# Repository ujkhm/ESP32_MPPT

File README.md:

# 微型發電機測試機 / Micro Generator Test Machine

以 **ESP32** 為核心的小型有刷直流發電機**特性量測機台**，不是 MPPT 控制器。

主動力 775 馬達把待測發電機帶到指定轉速後，依序量測連續安全電流、內阻與開路常數，再算出固定測試電阻上的功率曲線與可用轉速上限，上位機可存成 PDF 報表。

## 倉庫結構

```
micro-generator-test-machine
├── 3D_print_Component/   變速箱與機構 3D 模型（外殼 STL 另補）
├── BOM/                  元件清單與互動式 BOM
├── KiCad/                原理圖、PCB、Gerber
├── VSCode/esp32_code/    ESP32 韌體（PlatformIO）
└── Host computer/        免安裝上位機執行檔與說明
```

各資料夾內另有說明。

## 上位機

`Host computer/MicroGeneratorHost.exe` 免安裝。複製該資料夾到 Windows 電腦，雙擊執行，依畫面以藍牙連接下位機即可測試。詳見 [Host computer/README.md](./Host%20computer/README.md)。

## 目前狀態

- 電路與 PCB：完成（見 `KiCad/`、`BOM/`）
- 韌體量測流程：完成（安全電流、內阻、曲線）
- 上位機：完成（藍牙監控與 PDF 報表）
- 外殼：待補 STL

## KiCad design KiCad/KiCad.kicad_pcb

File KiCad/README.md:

## KiCad

本專案電路使用KiCad 9做開發，無修改原理圖/PCB需求的可以直接使用資料夾內的Gerber.zip檔直接提交給板廠製板<br><br>
附上原理突及PCB快照<br>
[原理圖](images/KiCad.pdf)<br>
[PCB](images/KiCad_PCB.pdf)<br>
建議下載後用 PDF 檢視工具開啟。快照位於 `KiCad/images/`。
另有BOM表單位於BOM資料夾下[點我前往](../BOM/README.md)<br>
[回到主頁](../README.md)

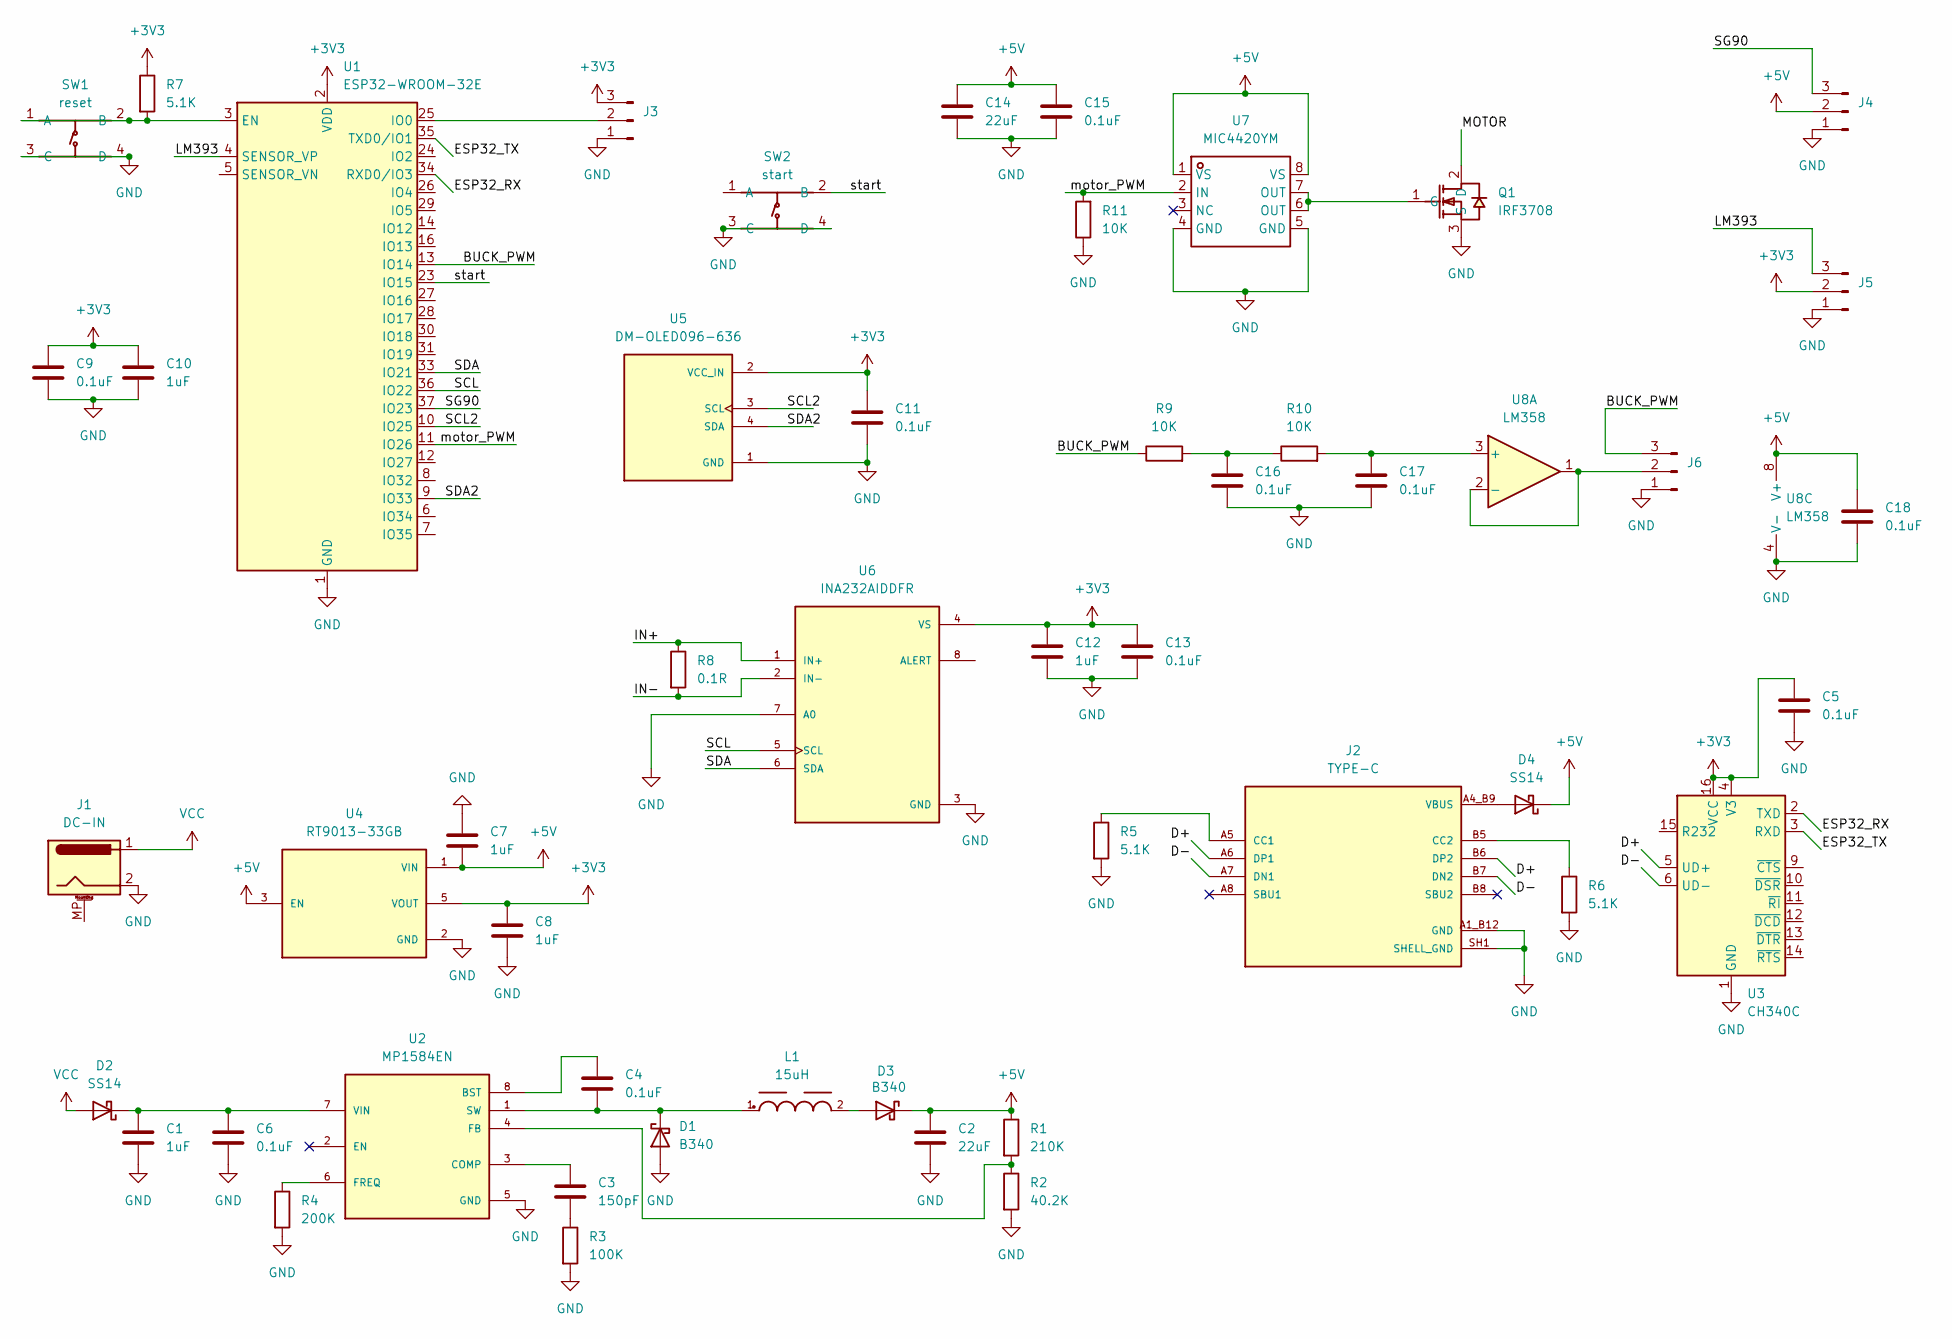
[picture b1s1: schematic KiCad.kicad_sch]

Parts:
C1, C7, C8, C10, C12: 1uF; C_0603_1608Metric
C2, C14: 22uF; C_0805_2012Metric
C3: 150pF; C_0603_1608Metric
C4, C5, C6, C9, C11, C13, C15, C16, C17, C18: 0.1uF; C_0603_1608Metric
D1, D3: B340; D_SMC
D2, D4: SS14; D_SMA
J1: DC-IN; BarrelJack_Kycon_KLDX-0202-xC_Horizontal
J2: TYPE-C; GCT_USB4105-GF-A; PARTREV B4
J3, J4, J5, J6: Conn_01x03_Pin; PinHeader_1x03_P2.54mm_Vertical
L1: 15uH; WE-PD_1260
Q1: IRF3708; TO-220-3_L10.0-W4.6-P2.54-L; LCSC Part C18212457
R1: 210K; R_0603_1608Metric
R2: 40.2K; R_0603_1608Metric
R3: 100K; R_0603_1608Metric
R4: 200K; R_0603_1608Metric
R5, R6, R7: 5.1K; R_0603_1608Metric
R8: 0.1R; R_2512_6332Metric
R9, R10, R11: 10K; R_0603_1608Metric
SW1: reset; SW-TH_4P-L6.0-W6.0-P4.50-LS6.5; LCSC Part C393938
SW2: start; SW-TH_4P-L6.0-W6.0-P4.50-LS6.5; LCSC Part C393938
U1: ESP32-WROOM-32E; ESP32-WROOM-32D
U2: MP1584EN; SOIC127P600X170-9N
U3: CH340C; SOIC-16_3.9x9.9mm_P1.27mm
U4: RT9013-33GB; SOT94P279X129-5N; PARTREV Aprill 2011
U5: DM-OLED096-636; MODULE_DM-OLED096-636; PARTREV 2018-09-10
U6: INA232AIDDFR; SOT65P280X110-8N; PARTREV December 2022
U7: MIC4420YM; SOIC-8_L4.9-W3.9-P1.27-LS6.0-BL; LCSC Part C637530
U8: LM358; SOIC-8_5.3x6.2mm_P1.27mm

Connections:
+3V3: C5.1, C8.1, C9.1, C10.1, C11.1, C12.1, C13.1, J3.3, J5.2, R7.1, U1.2 (VDD), U3.4 (V3), U3.16 (VCC), U4.5 (VOUT), U5.2 (VCC_IN), U6.4 (VS)
+5V: C2.1, C7.2, C14.1, C15.1, C18.1, D3.1 (K), D4.1 (K), J4.2, R1.1, U4.1 (VIN), U4.3 (EN), U7.1 (VS), U7.8 (VS), U8.8 (V+)
/BUCK_PWM: J6.3, R9.1, U1.13 (IO14)
/D+: J2.A6 (DP1), J2.B6 (DP2), U3.5 (UD+)
/D-: J2.A7 (DN1), J2.B7 (DN2), U3.6 (UD-)
/ESP32_RX: U1.34 (RXD0/IO3), U3.2 (TXD)
/ESP32_TX: U1.35 (TXD0/IO1), U3.3 (RXD)
/IN+: R8.1, U6.1 (IN+)
/IN-: R8.2, U6.2 (IN-)
/LM393: J5.3, U1.4 (SENSOR_VP)
/MOTOR: Q1.2 (D)
/SCL: U1.36 (IO22), U6.5 (SCL)
/SCL2: U1.10 (IO25), U5.3 (SCL)
/SDA: U1.33 (IO21), U6.6 (SDA)
/SDA2: U1.9 (IO33), U5.4 (SDA)
/SG90: J4.3, U1.37 (IO23)
/motor_PWM: R11.2, U1.11 (IO26), U7.2 (IN)
/start: SW2.2 (B), U1.23 (IO15)
GND: C1.2, C2.2, C5.2, C6.2, C7.1, C8.2, C9.2, C10.2, C11.2, C12.2, C13.2, C14.2, C15.2, C16.2, C17.2, C18.2, D1.2 (A), J1.2, J2.A1_B12 (GND), J2.B1_A12 (GND), J2.SH1 (SHELL_GND), J2.SH2 (SHELL_GND), J2.SH3 (SHELL_GND), J2.SH4 (SHELL_GND), J3.1, J4.1, J5.1, J6.1, Q1.3 (S), R2.2, R3.2, R4.2, R5.2, R6.2, R11.1, SW1.3 (C), SW1.4 (D), SW2.3 (C), SW2.4 (D), U1.1 (GND), U1.15 (GND), U1.38 (GND), U1.39 (GND), U2.5 (GND), U2.9 (GND), U3.1 (GND), U4.2 (GND), U5.1 (GND), U6.3 (GND), U6.7 (A0), U7.4 (GND), U7.5 (GND), U8.4 (V-)
unnamed: C3.2, R3.1
unnamed: C16.1, R9.2, R10.1
unnamed: C4.2, D1.1 (K), L1.1, U2.1 (SW)
unnamed: C1.1, C6.1, D2.1 (K), U2.7 (VIN)
unnamed: D3.2 (A), L1.2
unnamed: J2.A5 (CC1), R5.1
unnamed: J2.B5 (CC2), R6.1
unnamed: J3.2, U1.25 (IO0)
unnamed: J6.2, U8.1, U8.2 (-)
unnamed: Q1.1 (G), U7.6 (OUT), U7.7 (OUT)
unnamed: R7.2, SW1.1 (A), SW1.2 (B), U1.3 (EN)
unnamed: C4.1, U2.8 (BST)
unnamed: C3.1, U2.3 (COMP)
unnamed: R1.2, R2.1, U2.4 (FB)
unnamed: R4.1, U2.6 (FREQ)
unnamed: C17.1, R10.2, U8.3 (+)
VBUS: D4.2 (A), J2.A4_B9 (VBUS), J2.B4_A9 (VBUS)
VCC: D2.2 (A), J1.1

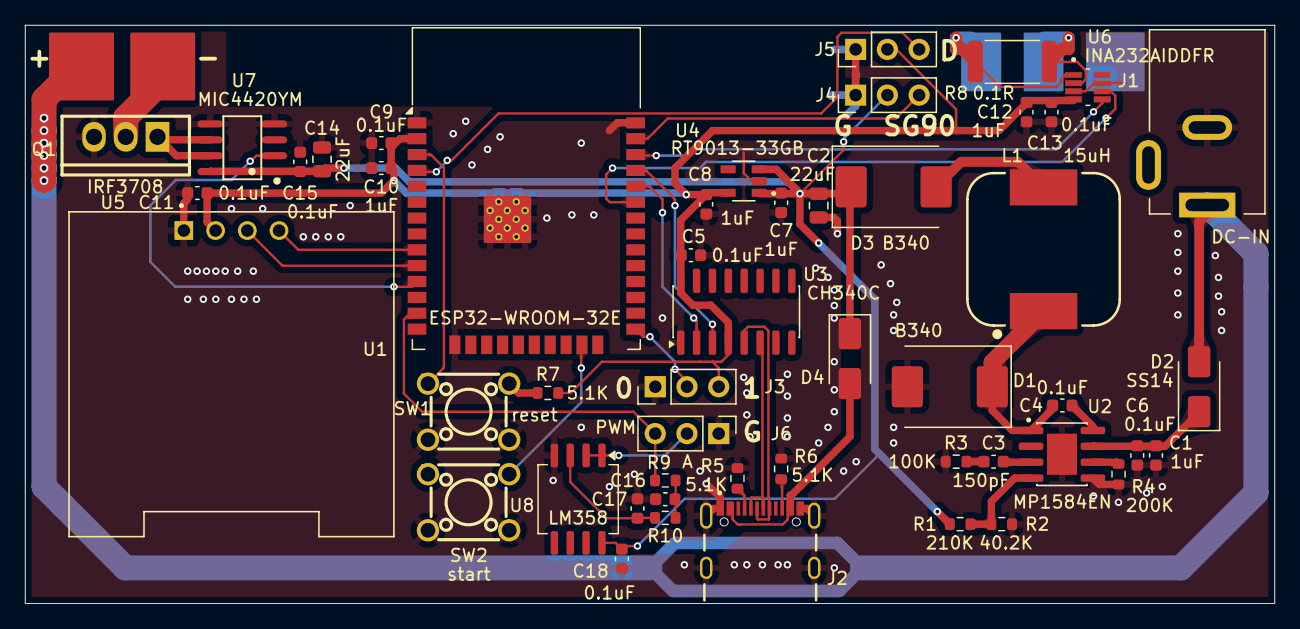
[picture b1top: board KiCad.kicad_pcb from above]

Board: 2 copper layers, 100.0 x 46.3 mm, 51 parts (1 on the bottom side), 36 nets.

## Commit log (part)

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2026-05-23 Add .gitignore for KiCad and development tools
2026-05-23 增加了ESP32核心的原理圖及PCB(不含供電)
2026-05-23 彻底移除KiCad临时文件，让.gitignore生效
2026-05-23 提交初始BOM表
2026-05-23 删除KiCad临时文件：autosave、backup、lock
2026-05-23 更新.gitignore：忽略KiCad的autosaved和backup文件夹
2026-05-23 移除已被追踪的KiCad自动保存文件夹
2026-05-23 提交修正後的.gitignore，修正#auto_saved_files#被上傳問題
2026-05-23 測試提交
2026-05-23 刪除#auto_saved_files#
2026-05-24 完成主電源輸入轉到數位系統主電源軌電壓(12~24v to 5v)之原理圖，包含外部DC供電接口
2026-05-24 完成主電源輸入轉到數位系統主電源軌電壓模塊(12~24v to 5v)之PCB
2026-05-25 更新BOM表
2026-05-25 完成5v電源軌的所有電路
2026-05-25 新增5V轉3.3V電源軌元件及防反接電路所需元件
2026-05-25 完成5V轉3.3V電源軌元件及防反接電路、ESP32復位電路、優化主電源輸入轉5V的電路、USB轉TTL完整迴路之原理突及PCB
2026-05-26 新增了vscode及3D_print_Component資料夾的自述文件
2026-05-26 完成esp32的燒錄/工作模式選擇電路之原理圖與PCB
2026-05-26 補全mcu供電去偶電容
2026-05-26 放置0.96吋OLED在園裡圖
2026-05-26 放置0.96吋OLED
2026-05-26 增加0.96'OLED(已完成原理圖及PCB)及開始測試按鈕(只添加到PCB，原理圖未連接)
2026-05-26 Update .gitignore to exclude Office temp files
    Add rules to ignore Microsoft Office temporary files
2026-05-26 delete~.XLSX
2026-05-26 完成start按鈕的原理圖/PCB連接
2026-05-26 修正OLED之SDA/SCL連接錯誤
2026-05-26 新增功率測量IC之原理圖及PCB(未連接)
2026-05-26 連接功率計IC的供電，新增MOS及驅動IC(未連接)
2026-05-27 完成pcb(除了DAC部分)
2026-05-27 補全功率測量迴路之電路
2026-05-29 修改iic走線，將原本共用同一組iic的裝置分別接到兩不同的iic
2026-05-29 完成PCB及原理圖所有的連接
2026-05-30 移除大面積焊盤上方的阻焊層
2026-05-30 增大外露銅箔接點之面積以利焊接
2026-05-30 增加Gerber製版文件
2026-05-30 修正被焊盤阻斷的絲印
2026-05-30 修改斯絲印位置
2026-05-30 完成bom表單
2026-05-30 更新README.md，新增ESP32_MPPT系統說明及文件架構；新增BOM及KiCad資料夾的README.md
2026-05-30 更新README.md，調整文件架構部分的格式，增加換行以提升可讀性
2026-05-30 新增多個README文件，包含專案結構及使用說明；新增.gitignore及platformio.ini配置文件；實作main.cpp及單元測試目錄
2026-05-30 更新 README.md
2026-05-31 新增ESP32速度傳感器功能，包含初始化函數及引腳定義，更新main.cpp以整合速度傳感器初始化，並新增clangd配置以改善IntelliSense支持。
2026-05-31 而成PINS.H
2026-05-31 修改速度感測模組的實現代碼
2026-06-01 完成測速模組(編譯未過)
2026-06-01 完成speed_sensor,h/.cpp
2026-06-01 更新環境
2026-06-01 補全pins.h
2026-06-01 新增簡單測試代碼
2026-06-02 嵌入freeRTOS以方便管理
2026-06-02 完善speed_sensor的延時方式，並新增motor_PID模組，且做了過去模組對RTOS的優化
2026-06-03 完成算完脈衝後即呼叫pid模組的功能
2026-06-04 初始化PWM函數
2026-06-04 更新reame.md
2026-06-07 增加變速箱之基礎齒輪
2026-06-07 修正reame.md之錯字
2026-06-08 更新readme.md
2026-06-08 更新自述文件
2026-06-08 新增電路中mic4420ym之驅動腳位下拉電阻
2026-06-08 更新自述文件，準備公開
2026-06-08 在自述文件說明進度
2026-06-08 增加授權說明條款
2026-06-08 修改自述文件
2026-06-08 Add MIT License to the project
2026-06-10 更新自述文件及變速箱
2026-06-10 回復自述文件舊版本
2026-06-10 Update README to clarify KiCad folder description
2026-06-11 新增快照
2026-06-13 新增光柵
2026-06-13 重新編寫測速模組底層代碼（未完成）
2026-06-15 完成speed_sensor模組的重建
2026-06-19 配置pid模塊
2026-06-25 繪製3d模型
